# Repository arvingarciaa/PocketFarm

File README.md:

# PocketFarm

## Abstract

PocketFarm aims to implement precision agriculture on a farm using a network of sensors and data from online weather sources. Low cost and efﬁcient sensors and microcontroller will be used to make an effective farm monitoring system to help the farmer monitor the irrigation. An efﬁcient irrigation system correlates to low cost farming and high yield of crops.

The project is based on a Philippine setting and may include Asia/Philippine-based stores and references.

## Use Case

Since this project is centered around ease of use and convenience, PocketFarm enables a semi-automatic irrigation system through text messaging, weather forecasts, and on-farm sensors. The farmer will have an electronic system integrated directly to their preferred mode of irrigation. Currently, we assume a [gravity irrigation system](https://www.youtube.com/watch?v=6-emq0cxhtU). 

![2]

---

## Project Components

### The Farm

To describe some the electronic components, a modified architectural diagram is presented as follows.

![1]

To clarify, the electronic system's brain is an [Arduino Uno (clone)](https://www.lazada.com.ph/arduino-uno-r3-arduino-compatible-board-with-usb-13329964.html?spm=a2o4l.searchlist.list.2.64ed7741O4s0hg), where two sensors--[Capacitive Soil Moisture Sensor](https://www.dfrobot.com/wiki/index.php/Capacitive_Soil_Moisture_Sensor_SKU:SEN0193), and a [DHT22 Temperature and Humidity Module](https://www.dfrobot.com/wiki/index.php/DHT22_Temperature_and_humidity_module_SKU:SEN0137)-- are connected, along with a [solenoid valve](https://www.makerlab-electronics.com/product/plastic-water-solenoid-valve-12v-1-2-nps/) which will control the irrigation system. In addition, a [GSM module](https://www.elecrow.com/sim800c-gprs-gsm-shield-for-arduino.html) serves as the communications link to the central remote server, which does all the processing and decisions.

### The Central Server

The central server is powered by a [Raspberry Pi](https://www.adafruit.com/product/998) hooked to the same [GSM module](https://www.elecrow.com/sim800c-gprs-gsm-shield-for-arduino.html) used in the farm setup. Additionally, the code is written in JavaScript, through Node.js to easily facilitate a front-end solution in the near future.

The server takes in all sensor data from all farm setups (soil moisture, temperature, and humidity), and their corresponding weather forecast data from [WeatherUnderground](https://www.wunderground.com). The server also facilitates scheduled farm irrigation, by sending commands to the farm setups.

---

## What's Inside

The repository contains the following directories.
```bash
./
|-- arduino/  
    # Contains all Arduino-related code, including previous revisions.
|-- server/  
    # Contains all server-related code, including previous revisions. They're meant to be run via Node.js.
|-- schematics/     
    # Contains all PCB schematics and layouts created for both the Raspberry Pi server setup and Arduino setup for the farm.
```

[1]: https://i.imgur.com/4u4o8eJ.png
[2]: https://i.imgur.com/9hq7tE3.png

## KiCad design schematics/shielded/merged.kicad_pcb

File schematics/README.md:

# PCB Fabrication at Home
This is a series of notes for me when I'm fabricating at home, so that I don't make the same mistakes next time. This was originally coming from PocketFarm-related experiences.

All of these are in a Philippine setting, and so will occasionally mention Philippine-based stores and retailers.

---

## Prerequisites
Most of the links here are from online stores, but they're usually _waaay_ cheaper when bought directly in-store (I think it's because the include the shipping costs with the product already, which isn't cost-effective when you're buying a lot from the same store; marketing tactics).
### Basic Stuff (buy and cut the board first!)
* a drill (_I use a Dremel 4000_)
* drill bits (_0.8mm, 1.0mm, 2.5mm, 3.0mm_)
* cut off wheel
* Presensitized PCB (_Kinsten, from e-Gizmo_)
* developer solution (_this came with the Presensitized PCB_)
### Layouting and UV Exposure
* Tracing Paper
* Laser Printer (_Inkjet apparently is equally fine, with a few quirks_)
* DIY UV exposure box (_Diploma Frame, a bunch of UV LEDs, a switch, a DC Jack_)
* Scissors
### Developing and Etching
* Muriatic Acid (_30% Hydrochloric Acid_)
* Hydrogen Peroxide (_Agua Oxigenada, larger volumes might be fine_)
* liquid containers (_I bought a 1L plastic container for the etching solution, and peanut butter jars for the developer solution_)
* two shallow containers for the developer solution and the etching solution
* face mask (_I use both a dust mask and earloop type mask from Mercury Drug_)
* safety goggles
* nitrile gloves (_I bought an industry-grade one for reusability_)
* glass funnel (_cannot emphasize how important this is_)
* nail polish (_acetone_)
* tissue paper (_lots_)
* absorbent cotton
### Placing and Soldering the Components
* soldering iron with a temperature knob (_mine came from China but [this](https://www.lazada.com.ph/adjustable-soldering-iron-60w-yihua-947-iii-8855270.html?spm=a2o4l.searchlist.list.2.34bd5748oZhjub) is basically it_)
* soldering [iron tip](https://www.makerlab-electronics.com/product/type-b-soldering-iron-tip/)
* solder (_Super Rubicon, 1 roll, 60%, 1.0m/m_)
* lead free tip tinner (_[Edsyn LT-1](https://www.lazada.com.ph/edsyn-lt-1-lead-free-soldering-tip-tinner-6777194.html), this is to revitalize the soldering tip_)
* blu-tack (_I'm using cheap transparent tape in the meantime._)
* desoldering pump or desoldering wick

---

## PCB Designing and Layouting
I'm using KiCad. I'm swearing by the Getting Started manual. Since I'm only doing single-sided designs, I always use the Back Layer. Here are my Design Rules for Pcbnew.

![1]

However, the clearance and the component vias are a bit small. I need to improve on this later.

Place some text on the Back Layer, and make sure it looks inverted. Print it on tracing paper (or transparency film) on a laser printer. When using an Inkjet Printer, make sure that the tracing paper doesn't jam, or curl during the process. Wet ink makes the tracing paper curl, and you may end up with an unusuable print. 

Make sure to inspect the print quality before proceeding.

## Exposing the Photoresist
Place the tracing paper where the printed side faces the PCB later on. You can check if this is the case by looking it through the ceiling, and you can read the text. Tape it into the glass frame, and once done (assuming that the board was already pre-cut), turn off the lights, peel the protective layer, and move quickly.

Place the PCB on the frame, aligned with the printout, lock the frame, and place it on the UV exposure box. Set the timer to 1 minute and 30 seconds, and turn on the lights. While this is happening, wear all protective equipment (goggles, mask, gloves).

## Developing the Exposed Board
The developer solution can be reused. Place caution into dissolving too much into the solution. The middle part of the PCB always develops last, and when this happens too slowly, add a little bit more of the developer powder. Adding too much developer powder will eat out photoresist on areas you don't intend to, and will lead to failure.

Inspect the board visually by rising it from time to time, and make sure you get everything covered (or erased).

## Etching and Exposing the Developed Board
I'm using Cupric Chloride as etchant. Some notes.
* Pure muriatic acid etches very, very quickly. It also produces a lot of fumes, noticeably making it a little bit harder to breathe.
* In the beginning, do a 1:1 ratio of HCl and H2O2.
* Add H2O2 when the solution begins to become olive green in color. Mix well.
* Add HCl when the copper isn't removed quickly. This is usually noticeable at the edges.
* Never add chemicals directly to the board. Do it on the side, then quickly agitate the solution.
* Cupric Chloride on Aqueous Hydrochloric Acid requires reoxidation. If this is done quite frequently, invest on an aquarium air pump (this will also do the agitation necessary for the board), or add H2O2 once in a while.
* CuCl stains. Make sure tissue is in standby nearby. I use a basin below the CuCl container to collect spilling etchant.
* If the recycled etchant doesn't work very well, start with a sizeable amount, then apply more HCl. This allows for a relatively faster etching process, without the excess fumes.
* When satisfied, remove the board from the etchant, dry it with tissue paper, and remove the photoresist with acetone (nail polish). You'd want to use this with cotton balls than tissue paper as cotton holds to the acetone for a little bit longer.
* When all copper components are exposed, clean the board (front and back with alcohol).
* Remember to follow your city guidelines on hazardous waste disposal. Never, ever, try to drain your chemicals directly down the sink!

## Drilling and Cutting the Etched Board
* Dremel 4000's speed works well set to 15--for cutting, drilling, and 5/10 for polishing.
* You'll get a lot of thin drill bits breaking easily, frequently. Make sure to have a lot of backup, and maybe invest on a Multi Chuck (Dremel 4486).
* I'm using a book as a vise/clamp. Invest in a better solution.
* Most through-hole components will work with 0.8mm, but 1.0mm breaks less frequently.
* Big holes are usually of the 3.0mm variant.
* DC jacks use a 2.5mm for the GND and the Switch, and a 3.0mm for the VCC.

## Soldering Through-Hole Components to the PCB
* Use blu-tack for temporarily fastening the components before soldering.
* Make sure to use a sharp tip rather than a tip with a flat end to make soldering jobs less ugly.

---
Take care!

[1]: https://i.imgur.com/gUOFxXU.png

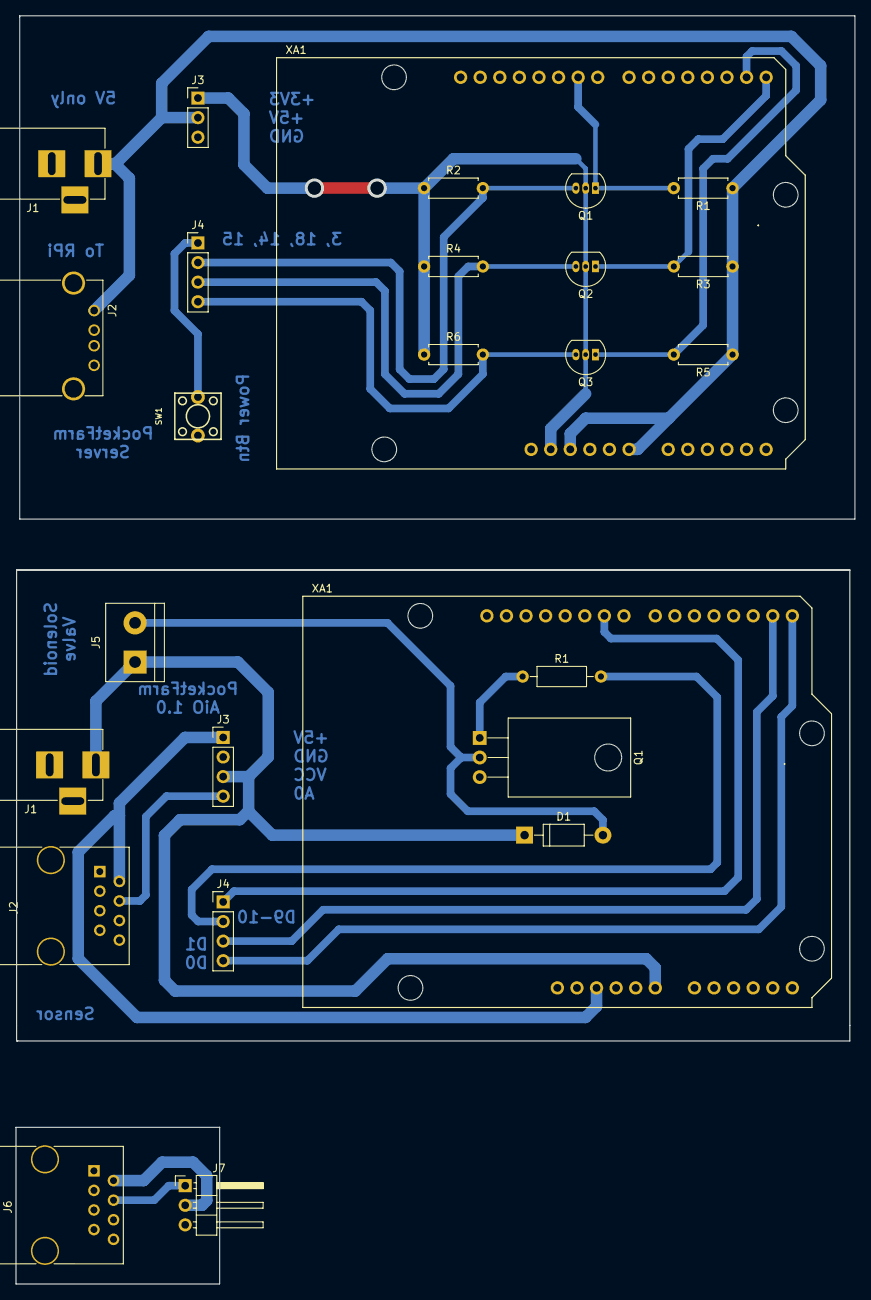
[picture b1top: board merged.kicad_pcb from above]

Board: 2 copper layers, 108.8 x 164.5 mm, 26 parts (0 on the bottom side), 37 nets.

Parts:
D1: 1N4001; D_DO-41_SOD81_P10.16mm_Horizontal
J1, J1#2: Jack-DC; BARREL_JACK
J2: USB_A
J2#2: RJ45_BUILTIN; RJ45_8
J3: Conn_01x03_Male; Pin_Header_Straight_1x03_Pitch2.54mm
J3#2, J4, J4#2: Conn_01x04_Male; Pin_Header_Straight_1x04_Pitch2.54mm
J5: Screw_Terminal_01x02; TerminalBlock_bornier-2_P5.08mm
J6: RJ45_SENSOR; RJ45_8
J7: Conn_01x03_Male; Pin_Header_Angled_1x03_Pitch2.54mm
Q1, Q2, Q3: 2N7000; TO-92_Inline_Narrow_Oval
Q1#2: TIP120; TO-220-3_Horizontal
R1, R2, R3, R4, R5, R6: 10k; R_Axial_DIN0207_L6.3mm_D2.5mm_P7.62mm_Horizontal
R1#2: 1k; R_Axial_DIN0207_L6.3mm_D2.5mm_P10.16mm_Horizontal
SW1: SW_SPST; SPST-2-PIN_6mm_thru
XA1, XA1#2: Arduino_Uno_Shield

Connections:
+3V3: J3.1, Q1.2, Q2.2, Q3.2, R2.1, R4.1, R6.1, XA1.3.3V
+5V: J1.1, J2.1, J2#2.2, J3.2, J3#2.1, J6.2, J7.2, R1.1, R3.1, R5.1, XA1.5V1, XA1.VIN, XA1#2.5V1
/A0: J2#2.4, J3#2.4, J6.4, J7.1
/D0_TX1: J4#2.4, XA1#2.D0
/D1_RX1: J4#2.3, XA1#2.D1
/D9: J4#2.1, XA1#2.D9
/D10: J4#2.2, R1#2.2
/GPIO3: J4.1, SW1.1
/GPIO18: J4.2, Q1.3, R2.2
/RXD0_15: J4.4, Q3.3, R6.2
/TXD0_14: J4.3, Q2.3, R4.2
GND: J1.2, J1#2.2, J2.4, J2#2.1, J2#2.3, J2#2.5, J2#2.6, J2#2.7, J2#2.8, J3.3, J3#2.2, J6.1, J6.3, J6.5, J6.6, J6.7, J6.8, J7.3, Q1#2.3, SW1.2, XA1.GND1, XA1.GND2, XA1.GND3, XA1#2.GND1, XA1#2.GND2, XA1#2.GND3
unnamed: D1.2, J5.2, Q1#2.2
unnamed: J1.3, J1#2.3
unnamed: Q1.1, Q1#2.1, R1.2, R1#2.1, XA1.D9
unnamed: Q2.1, R3.2, XA1.D0
unnamed: Q3.1, R5.2, XA1.D1
unnamed: XA1.A0, XA1#2.A0
unnamed: XA1.A1, XA1#2.A1
unnamed: XA1.A2, XA1#2.A2
unnamed: XA1.A3, XA1#2.A3
unnamed: XA1.A4, XA1#2.A4
unnamed: XA1.A5, XA1#2.A5
unnamed: XA1.AREF, XA1#2.AREF
unnamed: XA1.D2, XA1#2.D2
unnamed: XA1.D3, XA1#2.D3
unnamed: XA1.D4, XA1#2.D4
unnamed: XA1.D5, XA1#2.D5
unnamed: XA1.D6, XA1#2.D6
unnamed: XA1.D7, XA1#2.D7
unnamed: XA1.D8, XA1#2.D8
unnamed: XA1.D10, XA1#2.D10
unnamed: XA1.D11, XA1#2.D11
unnamed: XA1.D12, XA1#2.D12
unnamed: XA1.D13, XA1#2.D13
unnamed: XA1.RST1, XA1#2.RST1
VCC: D1.1, J1#2.1, J3#2.3, J5.1, XA1#2.VIN

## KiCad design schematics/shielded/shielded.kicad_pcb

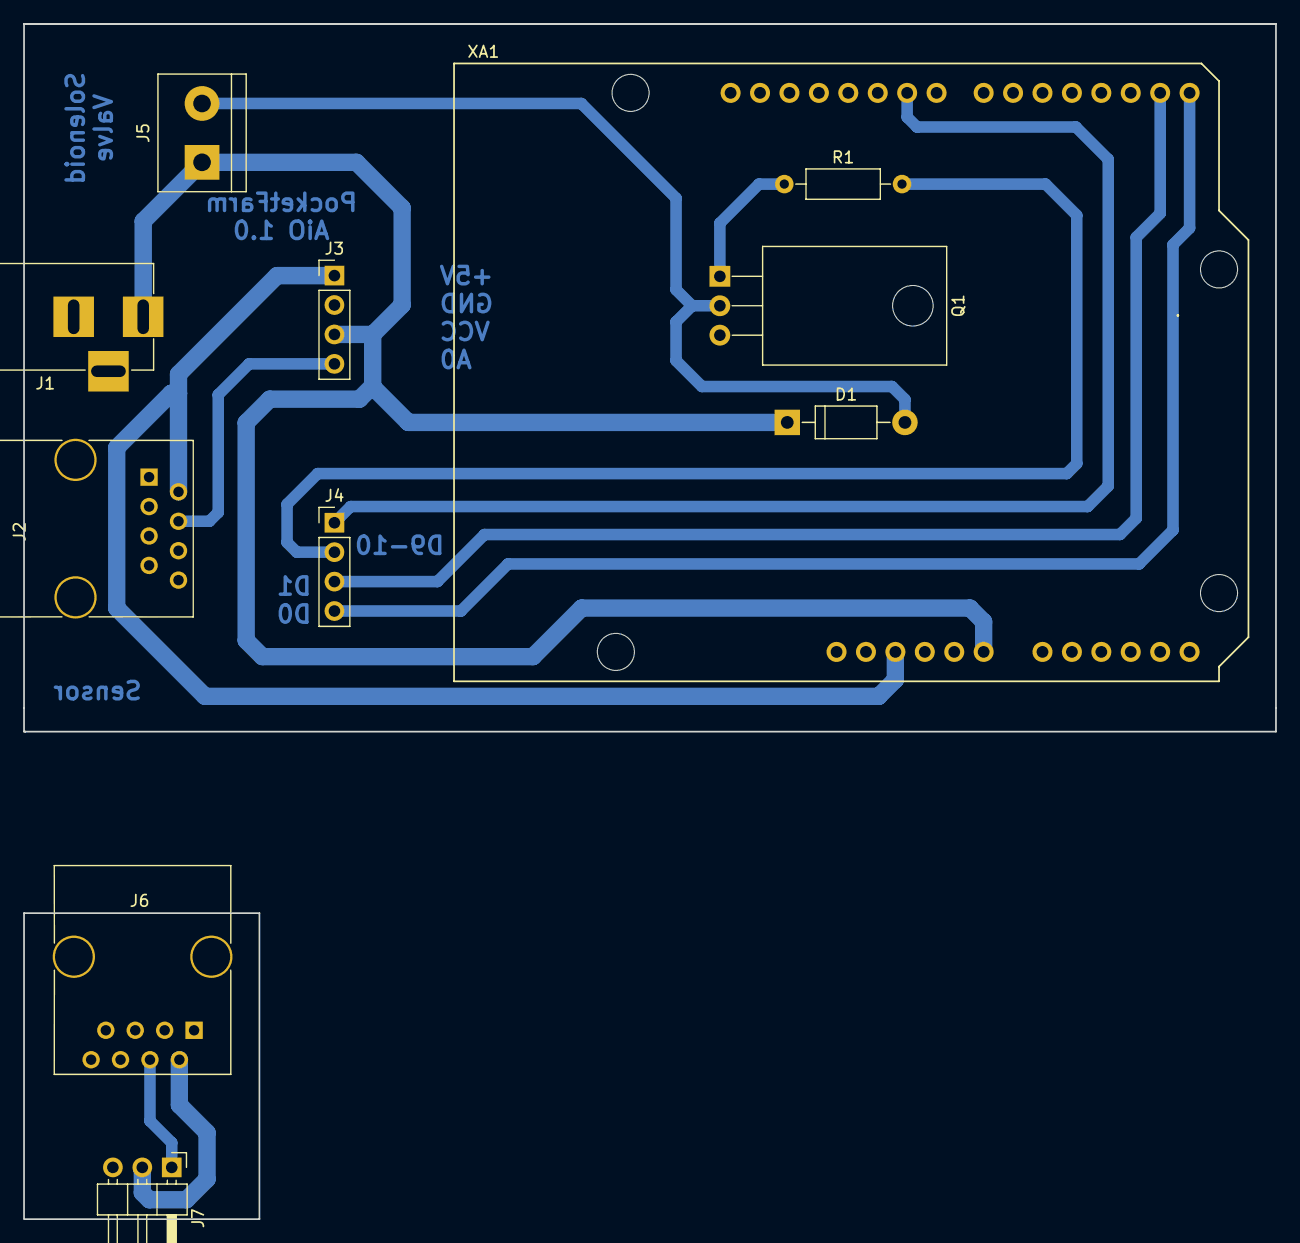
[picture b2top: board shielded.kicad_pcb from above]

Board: 2 copper layers, 108.1 x 61.1 mm, 11 parts (0 on the bottom side), 10 nets.

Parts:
D1: 1N4001; D_DO-41_SOD81_P10.16mm_Horizontal
J1: Jack-DC; BARREL_JACK
J2: RJ45_BUILTIN; RJ45_8
J3, J4: Conn_01x04_Male; Pin_Header_Straight_1x04_Pitch2.54mm
J5: Screw_Terminal_01x02; TerminalBlock_bornier-2_P5.08mm
J6: RJ45_SENSOR; RJ45_8
J7: Conn_01x03_Male; Pin_Header_Angled_1x03_Pitch2.54mm
Q1: TIP120; TO-220-3_Horizontal
R1: 1k; R_Axial_DIN0207_L6.3mm_D2.5mm_P10.16mm_Horizontal
XA1: Arduino_Uno_Shield

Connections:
+5V: J2.2, J3.1, J6.2, J7.2, XA1.5V1
/A0: J2.4, J3.4, J6.4, J7.1
/D0_TX1: J4.4, XA1.D0
/D1_RX1: J4.3, XA1.D1
/D9: J4.1, XA1.D9
/D10: J4.2, R1.2
GND: J1.2, J2.1, J2.3, J2.5, J2.6, J2.7, J2.8, J3.2, J6.1, J6.3, J6.5, J6.6, J6.7, J6.8, J7.3, Q1.3, XA1.GND1, XA1.GND2, XA1.GND3
unnamed: D1.2, J5.2, Q1.2
unnamed: Q1.1, R1.1
VCC: D1.1, J1.1, J3.3, J5.1, XA1.VIN

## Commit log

2018-01-12 Initial Files
2018-01-12 Changed name
2018-02-15 Add server code as well
2018-02-15 Relocate previous code to /arduino/v1/
2018-02-15 Add LICENSE
